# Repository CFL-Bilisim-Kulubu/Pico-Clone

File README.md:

# Pico-Clone by Mert Kalkancı
A Type-C using Raspberry Pi Pİco Clone, my fist big schematic &amp; pcb in Eagle Student Edition.
Hope you like it, it may can have some wrong connections I didn't printed & tested it also do not use this in a production, you can find better clones on the web.

It take around 5 hours to make, to contact me reach my profile.

[Schematic PDF](https://github.com/MertKalkanci/Pico-Clone/blob/main/outputs/schematic.pdf)

## Images

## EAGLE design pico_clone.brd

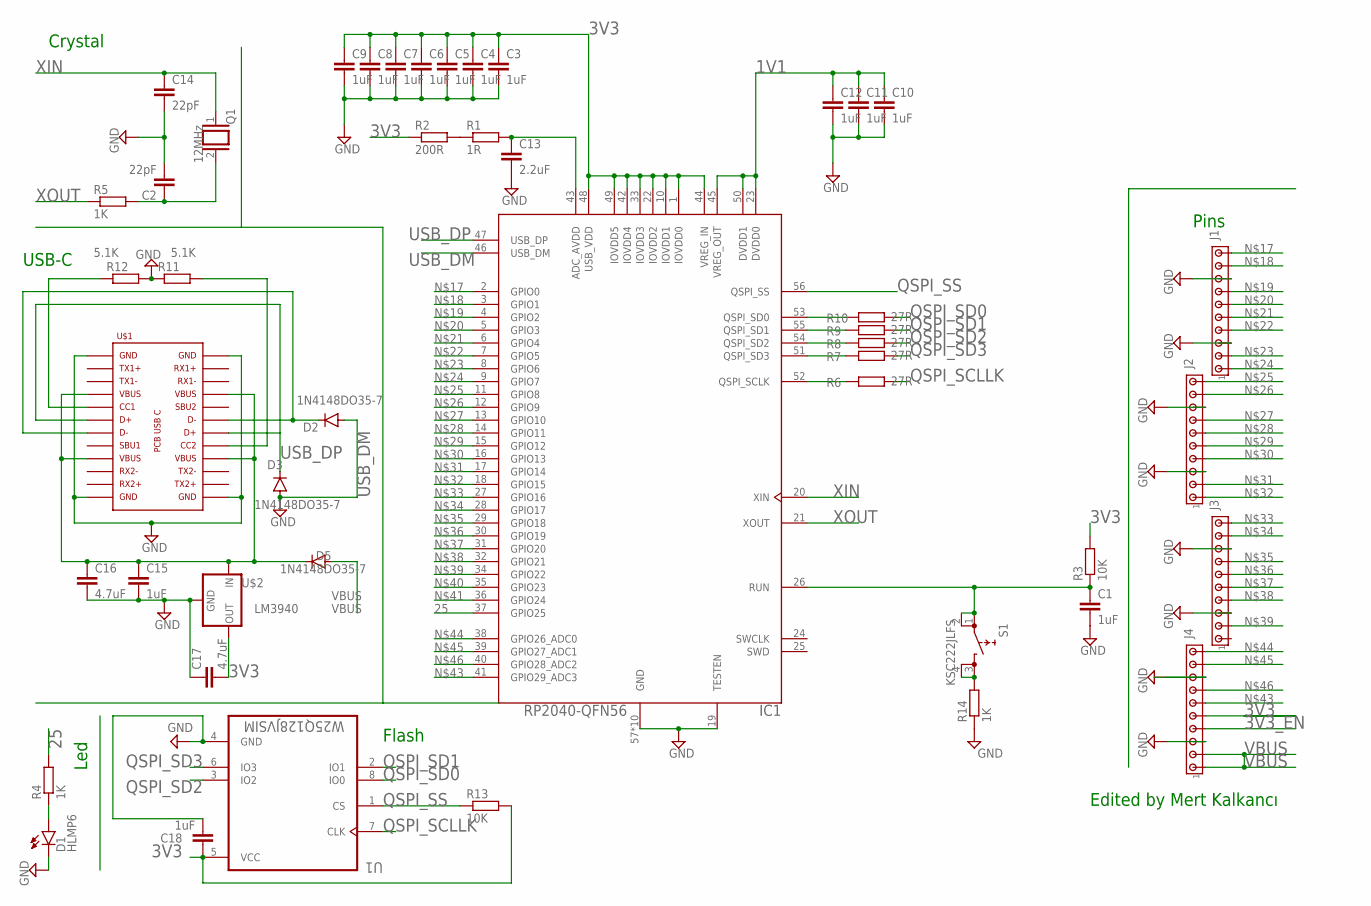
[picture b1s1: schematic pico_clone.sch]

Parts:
C1, C3, C4, C5, C6, C7, C8, C9, C10, C11, C12, C15, C18: 1uF; C2.5-3
C2, C14: 22pF; C2.5-3
C13: 2.2uF; C2.5-3
C16, C17: 4.7uF; C2.5-3
D1: HLMP6
D2, D3, D5: 1N4148DO35-7; DO35-7
IC1: RP2040-QFN56; RP2040-QFN-56
J1, J2, J3, J4: MTA10-100; 10X10MTA
Q1: 12MHz; QS
R1: 1R; M0805
R2: 200R; M0805
R3, R13: 10K; M0805
R4, R5, R14: 1K; M0805
R6, R7, R8, R9, R10: 27R; M0805
R11, R12: 5.1K; M0805
S1: KSC222JLFS
U1: W25Q128JVSIM; SOIC127P790X216-8N
U$1: PCB_USB_CDS_3; USB_TYPE_C_DS_3
U$2: LM3940; TO220

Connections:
1V1: C10.1, C11.1, C12.1, IC1.23 (DVDD0), IC1.45 (VREG_OUT), IC1.50 (DVDD1)
3V3: C3.1, C4.1, C5.1, C6.1, C7.1, C8.1, C9.1, C17.2, C18.1, IC1.1 (IOVDD0), IC1.10 (IOVDD1), IC1.22 (IOVDD2), IC1.33 (IOVDD3), IC1.42 (IOVDD4), IC1.44 (VREG_IN), IC1.48 (USB_VDD), IC1.49 (IOVDD5), J4.5, R2.1, R3.2, R13.2, U1.5 (VCC), U$2.3 (OUT)
3V3_EN: J4.4
25: IC1.37 (GPIO25), R4.2
GND: C1.2, C2.2, C3.2, C4.2, C5.2, C6.2, C7.2, C8.2, C9.2, C10.2, C11.2, C12.2, C13.2, C14.2, C15.2, C16.2, C17.1, C18.2, D1.K, D2.A, D3.A, IC1.19 (TESTEN), IC1.57 (GND), IC1.58 (GND), IC1.59 (GND), IC1.60 (GND), IC1.61 (GND), IC1.62 (GND), IC1.63 (GND), IC1.64 (GND), IC1.65 (GND), IC1.66 (GND), J1.3, J1.8, J2.3, J2.8, J3.3, J3.8, J4.3, R11.1, R12.2, R14.1, U1.4 (GND), U$1.A1, U$1.A12, U$1.B1, U$1.B12, U$2.2 (GND)
unnamed: R1.1, R2.2
unnamed: C13.1, IC1.43 (ADC_AVDD), R1.2
unnamed: IC1.52 (QSPI_SCLK), R6.1
unnamed: D1.A, R4.1
unnamed: C2.1, Q1.2, R5.2
unnamed: IC1.51 (QSPI_SD3), R7.1
unnamed: IC1.54 (QSPI_SD2), R8.1
unnamed: IC1.55 (QSPI_SD1), R9.1
unnamed: IC1.53 (QSPI_SD0), R10.1
unnamed: C15.1, C16.1, D5.C, U$1.A4, U$1.A9, U$1.B4, U$1.B9, U$2.1 (IN)
unnamed: R11.2, U$1.B5
unnamed: R12.1, U$1.A5
unnamed: IC1.2 (GPIO0), J1.10
unnamed: IC1.3 (GPIO1), J1.9
unnamed: IC1.4 (GPIO2), J1.7
unnamed: IC1.5 (GPIO3), J1.6
unnamed: IC1.6 (GPIO4), J1.5
unnamed: IC1.7 (GPIO5), J1.4
unnamed: IC1.8 (GPIO6), J1.2
unnamed: IC1.9 (GPIO7), J1.1
unnamed: IC1.11 (GPIO8), J2.10
unnamed: IC1.12 (GPIO9), J2.9
unnamed: IC1.13 (GPIO10), J2.7
unnamed: IC1.14 (GPIO11), J2.6
unnamed: IC1.15 (GPIO12), J2.5
unnamed: IC1.16 (GPIO13), J2.4
unnamed: IC1.17 (GPIO14), J2.2
unnamed: IC1.18 (GPIO15), J2.1
unnamed: IC1.27 (GPIO16), J3.10
unnamed: IC1.28 (GPIO17), J3.9
unnamed: IC1.29 (GPIO18), J3.7
unnamed: IC1.30 (GPIO19), J3.6
unnamed: IC1.31 (GPIO20), J3.5
unnamed: IC1.32 (GPIO21), J3.4
unnamed: IC1.34 (GPIO22), J3.2
unnamed: R14.2, S1.3, S1.4
unnamed: IC1.41 (GPIO29_ADC3), J4.6
unnamed: IC1.38 (GPIO26_ADC0), J4.10
unnamed: IC1.39 (GPIO27_ADC1), J4.9
unnamed: IC1.40 (GPIO28_ADC2), J4.7
QSPI_SCLLK: R6.2, U1.7 (CLK)
QSPI_SD0: R10.2, U1.8 (IO0)
QSPI_SD1: R9.2, U1.2 (IO1)
QSPI_SD2: R8.2, U1.3 (IO2)
QSPI_SD3: R7.2, U1.6 (IO3)
QSPI_SS: IC1.56 (QSPI_SS), R13.1, U1.1 (CS)
RST: C1.1, IC1.26 (RUN), R3.1, S1.1, S1.2
USB_DM: D2.C, IC1.46 (USB_DM), U$1.A7, U$1.B7
USB_DP: D3.C, IC1.47 (USB_DP), U$1.A6, U$1.B6
VBUS: D5.A, J4.1, J4.2
XIN: C14.1, IC1.20 (XIN), Q1.1
XOUT: IC1.21 (XOUT), R5.1

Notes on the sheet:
Edited by Mert Kalkancı
Pins
Led
Crystal
USB-C
Flash

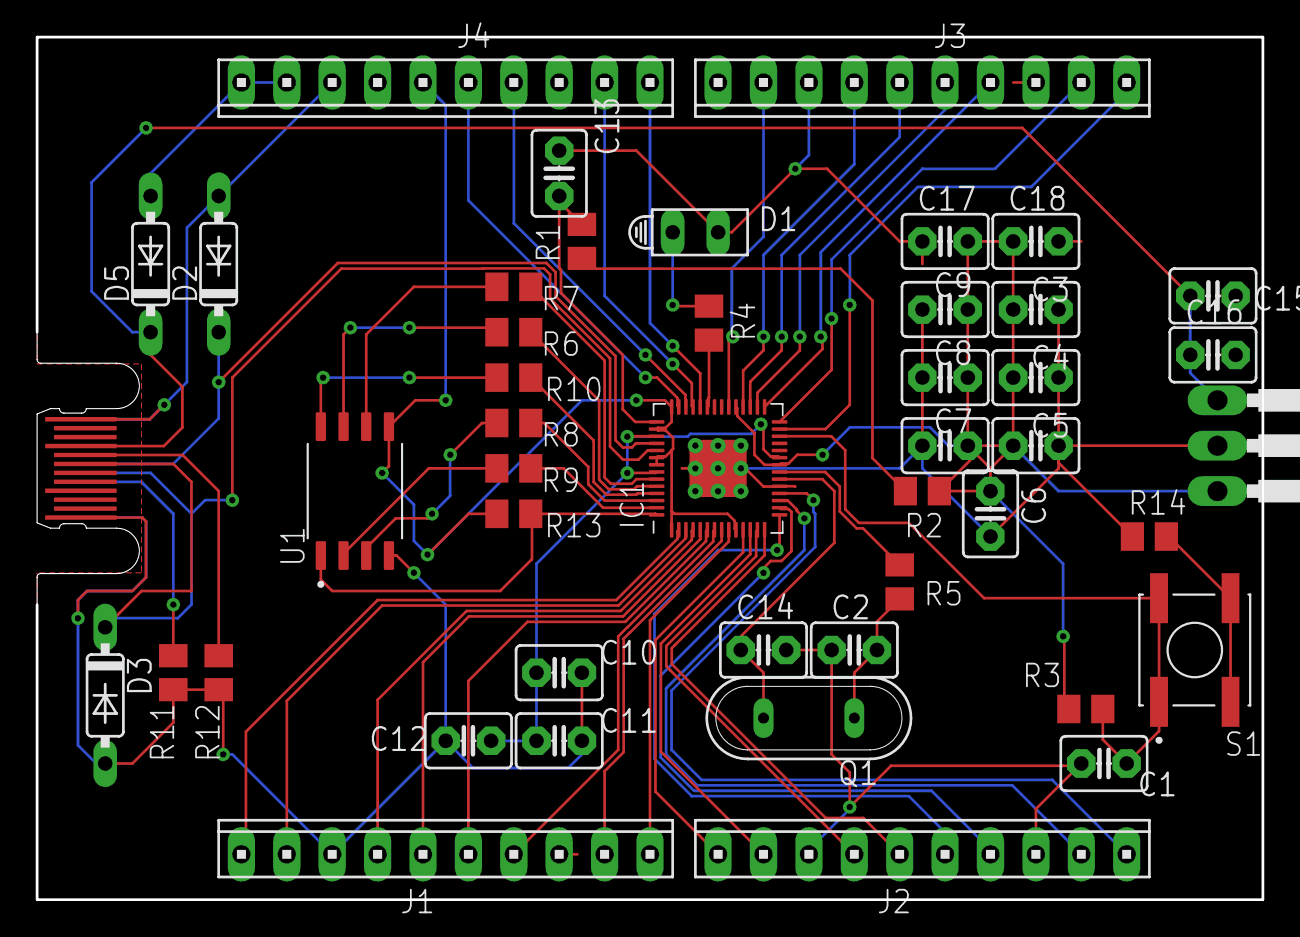
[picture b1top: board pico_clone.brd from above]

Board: 2 copper layers, 68.6 x 48.3 mm, 46 parts (0 on the bottom side), 56 nets.

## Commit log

2023-08-30 update gnd & unmatchet pins
2023-08-30 export libraries
2023-08-30 not sure what this files does
